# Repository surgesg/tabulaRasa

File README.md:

# tabulaRasa

The tabulaRasa is a digital wavetable oscillator with voltage control of frequency, waveform selection, 
and the amount of interpolation between waveforms. 
The tabulaRasa consists of two components: a hardware synthesis module which can integrate
into a modular synth system, and a software application which allows the user to create their own custom waveforms. 
These waveforms are then transferred from the computer to the tabulaRasa module through a standard SD card slot.

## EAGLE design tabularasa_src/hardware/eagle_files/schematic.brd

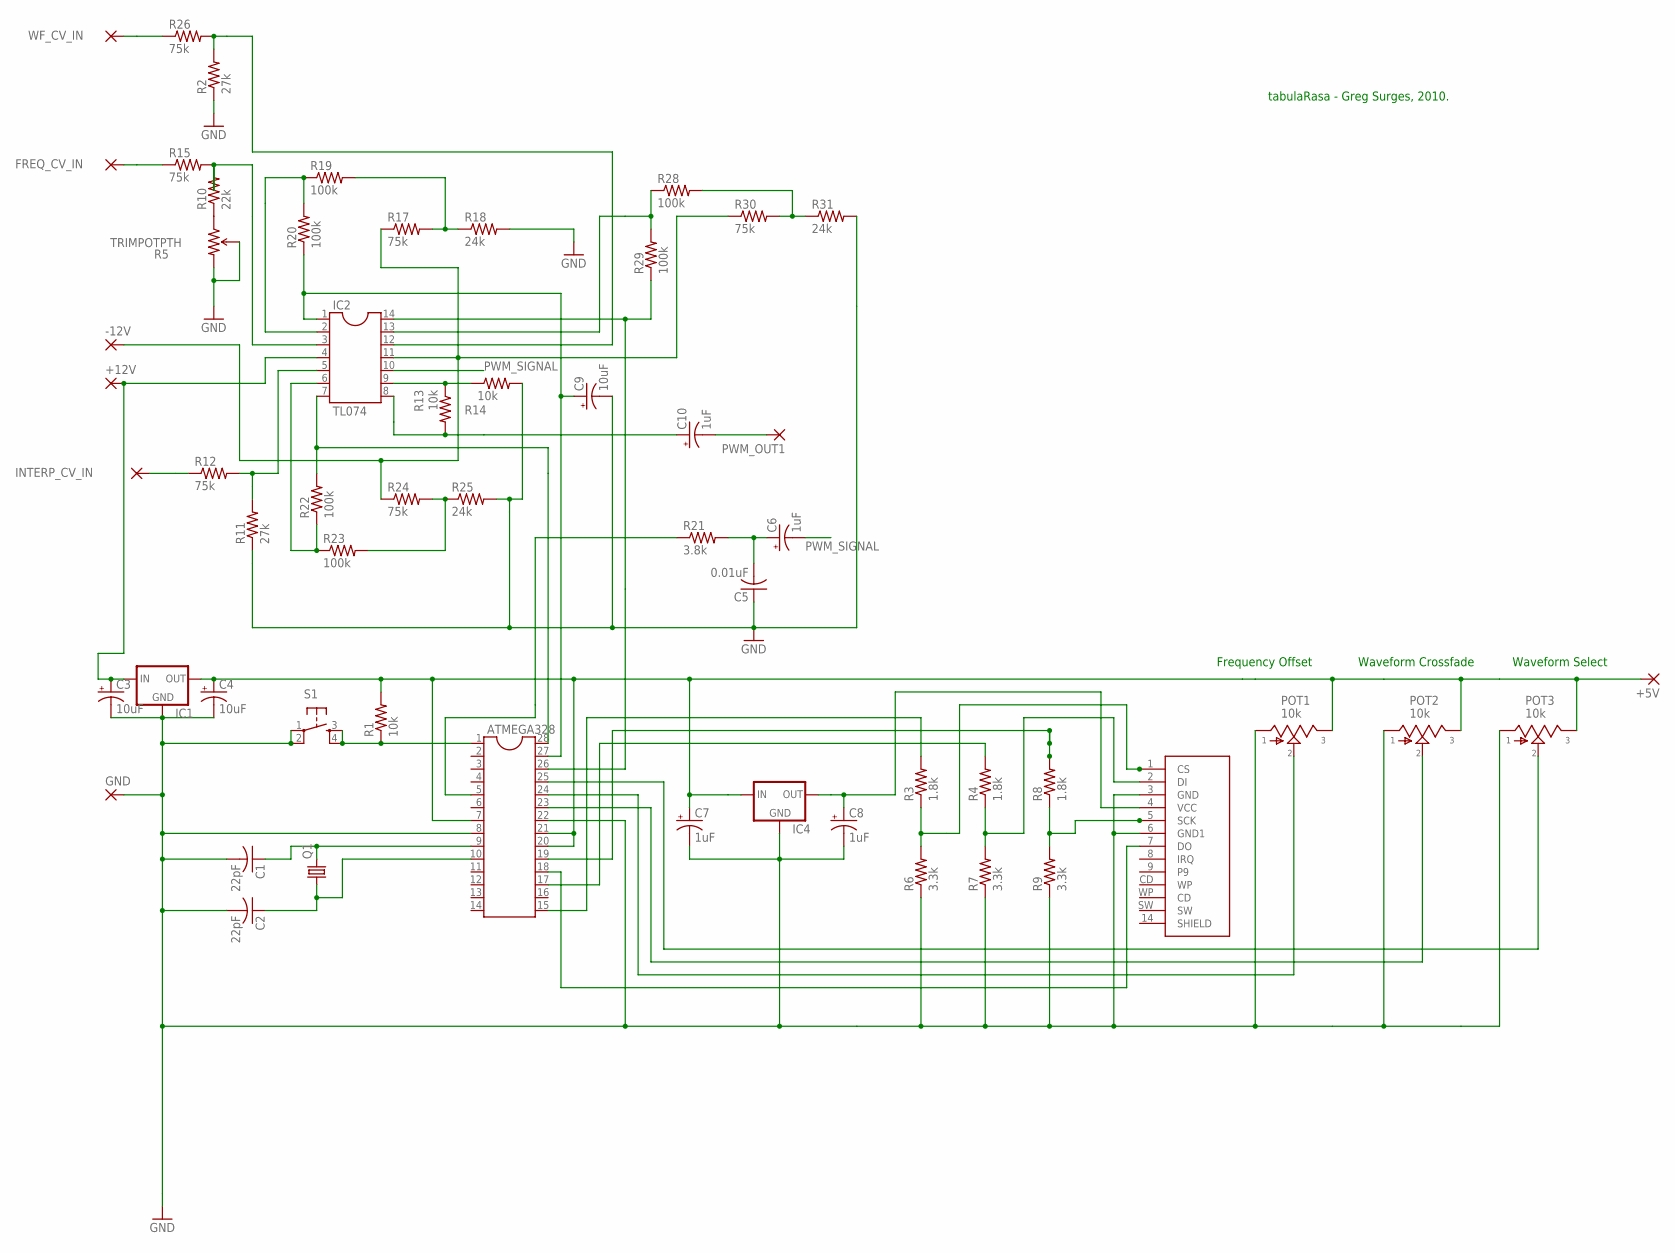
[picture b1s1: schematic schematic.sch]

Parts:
+5V, +12V: 3,81/1,4
-12V: 3,81/1,4
ATMEGA328: DIL28-3
C1, C2: 22pF; C050-025X075
C3, C4, C9: 10uF; E2,5-6
C5: 0.01uF; C050-025X075
C6, C7, C8, C10: 1uF; E2,5-6
FREQ_CV_IN: 3,81/1,4
GND: 3,81/1,4
IC1: V_REG_78XXSIDE; 78XXL
IC2: TL074; DIL14
IC4: MCP1700INLINE; TO92-INLINE
INTERP_CV_IN: 3,81/1,4
POT1, POT2, POT3: 10k; 16MM-PCB-MOUNT
PWM_OUT1: 3,81/1,4
Q1: CRYSTALHC49US; HC49US
R1, R13, R14: 10k; 0411/12
R2, R11: 27k; 0411/12
R3, R4, R8: 1.8k; 0411/12
R5: TRIMPOTPTH; TRIM_POT_PTH
R6, R7, R9: 3.3k; 0411/12
R10: 22k; 0411/12
R12, R15, R17, R24, R26, R30: 75k; 0411/12
R18, R25, R31: 24k; 0411/12
R19, R20, R22, R23, R28, R29: 100k; 0411/12
R21: 3.8k; 0411/12
S1: TAC_SWITCHPTH; TACTILE-PTH
U$1: SD_CARD_SOCKETSD; SD-MMC_SOCKET-PP
WF_CV_IN: 3,81/1,4

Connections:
GND: ATMEGA328.8, ATMEGA328.22, C1.2, C2.2, C3.-, C4.-, C5.1, C7.-, C8.-, C9.-, GND.1, IC1.GND, IC4.1 (GND), POT1.1, POT2.1, POT3.1, R2.1, R5.2 (WIPER), R5.3 (CW), R6.1, R7.1, R9.1, R11.1, R14.2, R18.2, R25.2, R31.2, S1.1, S1.2, U$1.3 (GND), U$1.6 (GND1)
unnamed: C8.+, IC4.3 (OUT), U$1.4 (VCC)
unnamed: +5V.1, ATMEGA328.7, ATMEGA328.20, ATMEGA328.21, C4.+, C7.+, IC1.OUT, IC4.2 (IN), POT1.3, POT2.3, POT3.3, R1.2
unnamed: R3.1, R6.2, U$1.1 (CS)
unnamed: ATMEGA328.1, R1.1, S1.3, S1.4
unnamed: R4.1, R7.2, U$1.2 (DI)
unnamed: ATMEGA328.9, C1.1, Q1.2
unnamed: ATMEGA328.10, C2.1, Q1.1
unnamed: INTERP_CV_IN.1, R12.1
unnamed: ATMEGA328.18, U$1.7 (DO)
unnamed: R5.1 (CCW), R10.1
unnamed: R8.1, R9.2, U$1.5 (SCK)
unnamed: ATMEGA328.15, R3.2
unnamed: ATMEGA328.24, POT1.2
unnamed: ATMEGA328.17, R4.2
unnamed: ATMEGA328.19, R8.2
unnamed: ATMEGA328.23, POT2.2
unnamed: ATMEGA328.25, POT3.2
unnamed: +12V.1, C3.+, IC1.IN, IC2.4
unnamed: IC2.2, R19.1, R20.2
unnamed: ATMEGA328.28, IC2.7, R22.2
unnamed: IC2.6, R22.1, R23.1
unnamed: FREQ_CV_IN.1, R15.1
unnamed: IC2.9, R13.1, R14.1
unnamed: ATMEGA328.27, C9.+, IC2.1, R20.1
unnamed: R17.2, R18.1, R19.2
unnamed: R28.2, R30.2, R31.1
unnamed: ATMEGA328.5, R21.1
unnamed: C5.2, C6.+, R21.2
unnamed: R23.2, R24.2, R25.1
unnamed: R26.1, WF_CV_IN.1
unnamed: IC2.12, R2.2, R26.2
unnamed: IC2.13, R28.1, R29.2
unnamed: ATMEGA328.26, IC2.14, R29.1
unnamed: -12V.1, IC2.11, R17.1, R24.1, R30.1
unnamed: C10.-, PWM_OUT1.1
unnamed: IC2.3, R10.2, R15.2
unnamed: IC2.5, R11.2, R12.2
OUTPUT: C10.+, IC2.8, R13.2
PWM_SIGNAL: C6.-, IC2.10

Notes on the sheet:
Frequency Offset
Waveform Crossfade
Waveform Select
tabulaRasa - Greg Surges, 2010.

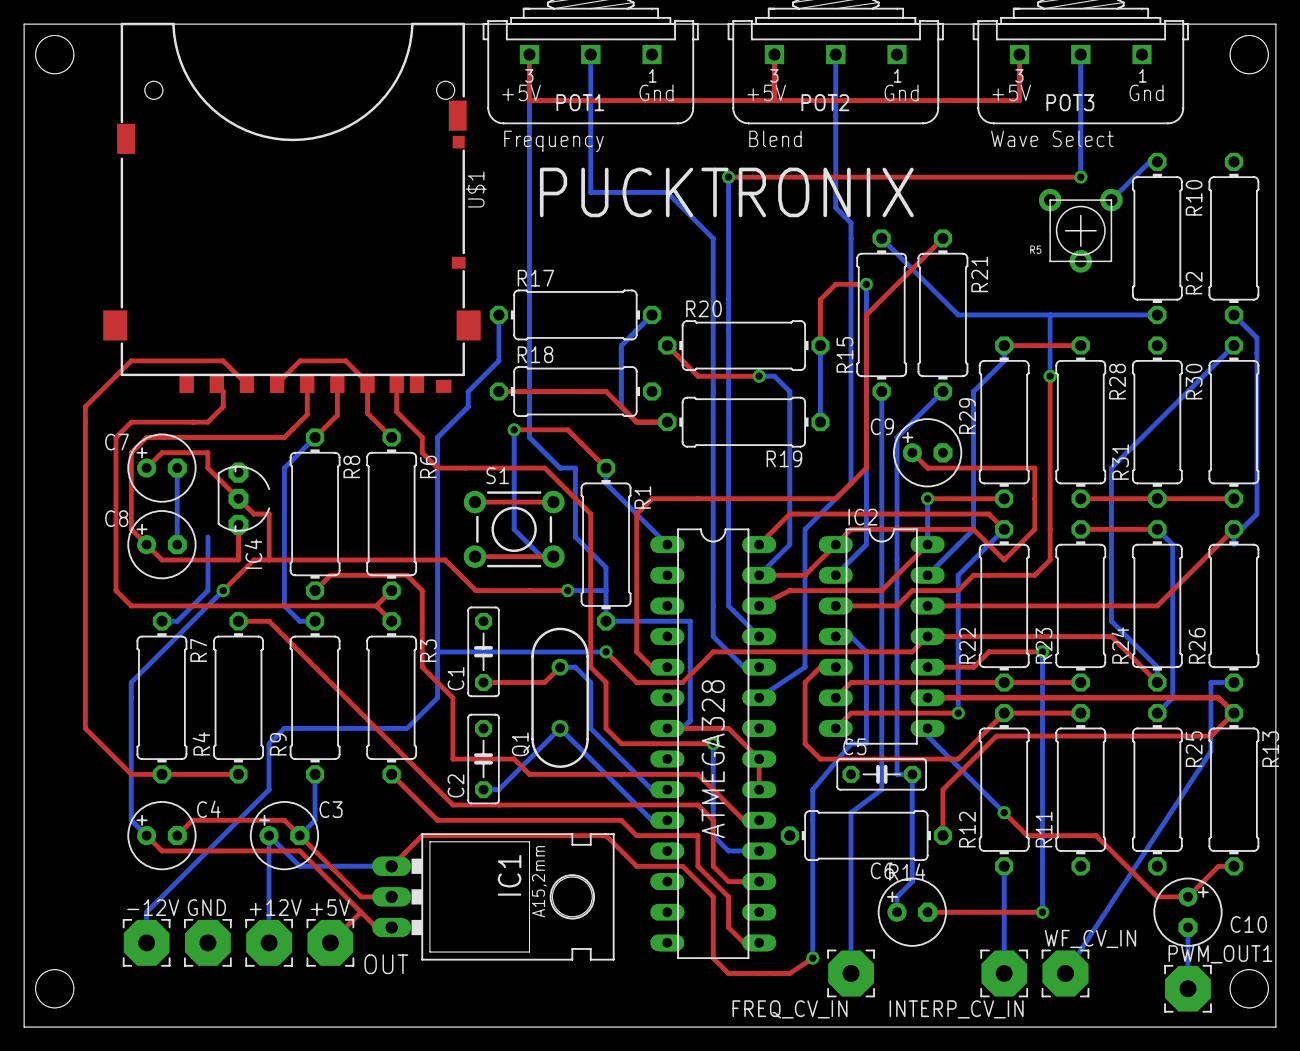
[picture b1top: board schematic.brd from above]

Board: 2 copper layers, 103.8 x 83.2 mm, 57 parts (0 on the bottom side), 40 nets.

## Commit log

2016-07-05 restructured and added GPL
2016-07-05 resturcturing
2016-07-05 added GPL file
2016-07-05 restructure
2016-07-05 added hardware files
2016-07-05 removed .svn folder
2016-07-05 added schematic

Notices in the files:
parts and their libraries:
SparkFun-Electromechanical: Licensing: CC v3.0 Share-Alike You are welcome to use this library for commercial purposes.
